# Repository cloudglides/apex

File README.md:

<h1 align="center">
  <br>

  <br>
  Apex
  <br>
</h1>
<h4 align="center">
A hub worth looking at.
</h4>
<div align="center">

</div>
<p align="center">
  <a href="#pcb">PCB</a> •
  <a href="#credits">Credits</a> •
  <a href="https://cad.onshape.com/documents/b957cb9eaff1fd55d943d2a3/w/8976d83a889d159a1f08a7bd/e/cf5443223244322f256cbf86">OnShape</a>
</p>

Apex is a custom usb hub PCB built around the Seeed FE1.1S, packing 1 upstream usb-c port, 2 downstream usb-a port.
Built because most usb hub don't let you own what's inside. Apex is made to be reproducible.

## PCB

Designed in KiCad with attention to power management, and equal traces. The board features a 2-layer optimized routing.

## How To build it?

Pretty simple actually, source all the components in BOM and assemble the pcb 
(the project uses smd components so get a pcba if you dont got prior experience)

## Why i made it?

- i wanted to make something
- i had nothing else to make
- i dont got a usb hub either and i really need it

### Schematic

---

### PCB Layers

#### Layer 1

#### Layer 2

---

### Board Views

#### Front

#### Back

### Zine

## Credits

This project uses:
- [KiCad](https://www.kicad.org/)
- [OnShape](https://cad.onshape.com/) for cad
- [Hack Club Fallout](https://fallout.hackclub.com)

## License

GPL

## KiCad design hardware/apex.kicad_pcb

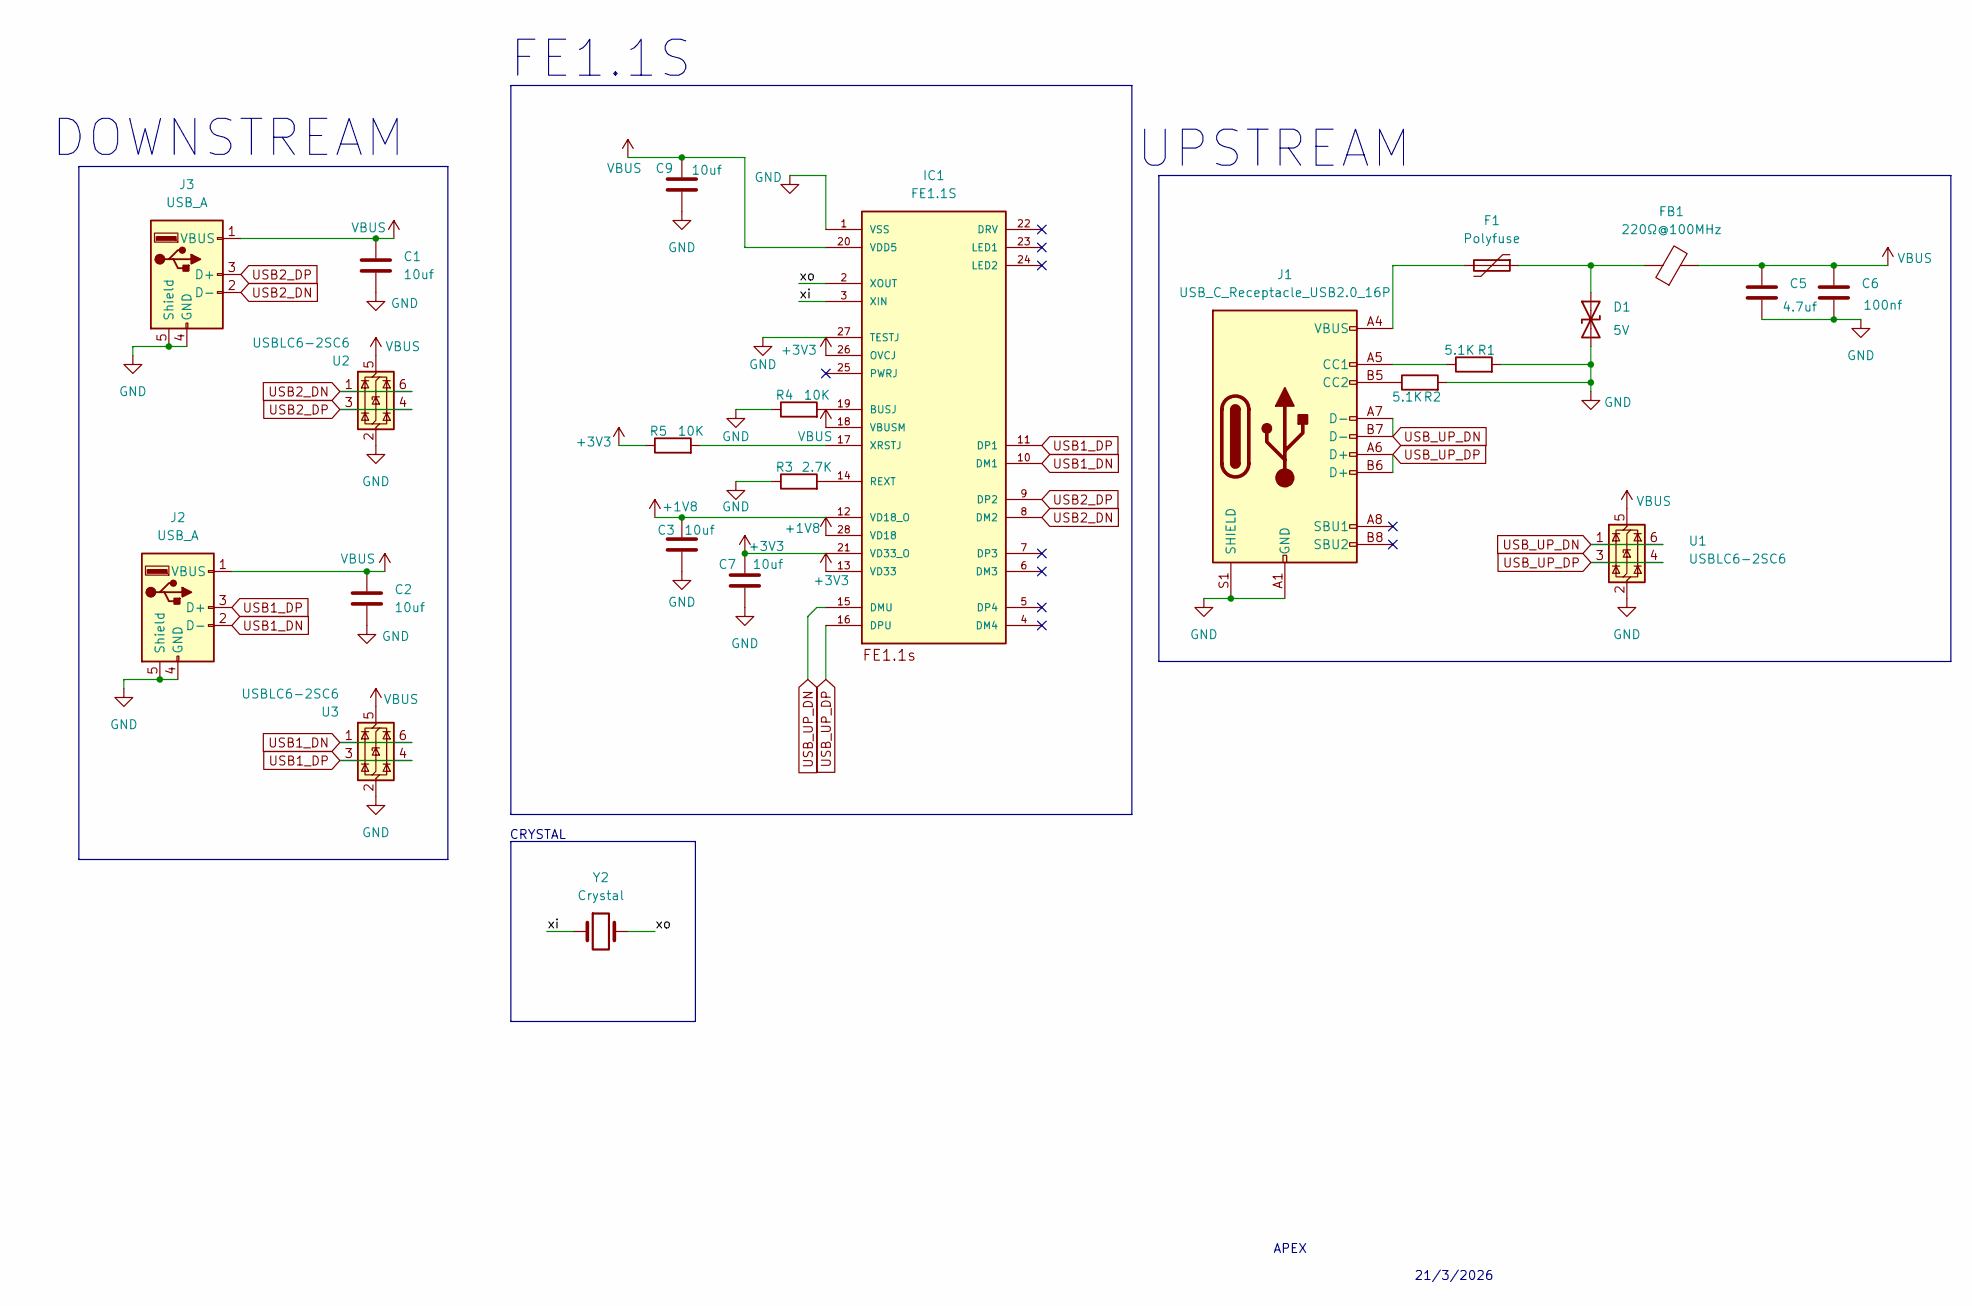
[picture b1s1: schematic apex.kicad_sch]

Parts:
C1, C2, C3, C7, C9: 10uf; C_0805_2012Metric
C5: 4.7uf; C_0805_2012Metric
C6: 100nf; C_0603_1608Metric
D1: 5V; D_SOD-123; LCSC Part C82044
F1: Polyfuse; Fuse_1206_3216Metric
FB1: 220Ω@100MHz; L_0603_1608Metric
IC1: FE1.1S; FE1.1S_SSOP-28
J1: USB_C_Receptacle_USB2.0_16P; USB_C_Receptacle_XKB_U262-16XN-4BVC11
J2, J3: USB_A; USB_A_Connfly_DS1095
R1, R2: 5.1K; R_0603_1608Metric
R3: 2.7K; R_0603_1608Metric
R4, R5: 10K; R_0603_1608Metric
U1, U2, U3: USBLC6-2SC6; SOT-23-6
Y2: Crystal; Crystal_SMD_HC49-SD

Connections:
+1V8: C3.1, IC1.12 (VD18_O), IC1.28 (VD18)
+3V3: C7.1, IC1.13 (VD33), IC1.21 (VD33_O), IC1.26 (OVCJ), R5.1
/xi: IC1.3 (XIN), Y2.1
/xo: IC1.2 (XOUT), Y2.2
GND: C1.2, C2.2, C3.2, C5.2, C6.2, C7.2, C9.2, D1.2 (A2), IC1.1 (VSS), IC1.27 (TESTJ), J1.A1 (GND), J1.A12 (GND), J1.B1 (GND), J1.B12 (GND), J1.S1 (SHIELD), J2.4 (GND), J2.5 (Shield), J3.4 (GND), J3.5 (Shield), R1.2, R2.2, R3.1, R4.1, U1.2 (GND), U2.2 (GND), U3.2 (GND)
unnamed: D1.1 (A1), F1.1, FB1.1
unnamed: F1.2, J1.A4 (VBUS), J1.A9 (VBUS), J1.B4 (VBUS), J1.B9 (VBUS)
unnamed: IC1.19 (BUSJ), R4.2
unnamed: IC1.14 (REXT), R3.2
unnamed: IC1.17 (XRSTJ), R5.2
unnamed: J1.A5 (CC1), R1.1
unnamed: J1.B5 (CC2), R2.1
USB1_DN: IC1.10 (DM1), J2.2 (D-), U3.1 (I/O1), U3.6 (I/O1)
USB1_DP: IC1.11 (DP1), J2.3 (D+), U3.3 (I/O2), U3.4 (I/O2)
USB2_DN: IC1.8 (DM2), J3.2 (D-), U2.1 (I/O1), U2.6 (I/O1)
USB2_DP: IC1.9 (DP2), J3.3 (D+), U2.3 (I/O2), U2.4 (I/O2)
USB_UP_DN: IC1.15 (DMU), J1.A7 (D-), J1.B7 (D-), U1.1 (I/O1), U1.6 (I/O1)
USB_UP_DP: IC1.16 (DPU), J1.A6 (D+), J1.B6 (D+), U1.3 (I/O2), U1.4 (I/O2)
VBUS: C1.1, C2.1, C5.1, C6.1, C9.1, FB1.2, IC1.18 (VBUSM), IC1.20 (VDD5), J2.1 (VBUS), J3.1 (VBUS), U1.5 (VBUS), U2.5 (VBUS), U3.5 (VBUS)

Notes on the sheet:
21/3/2026
CRYSTAL
FE1.1S
DOWNSTREAM
UPSTREAM
APEX

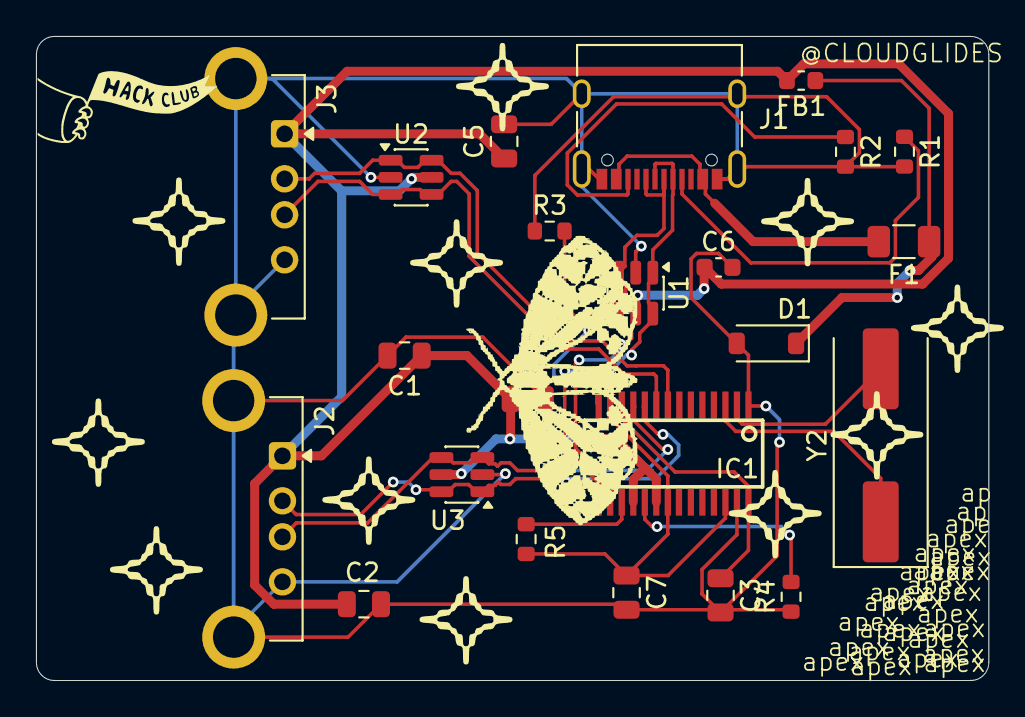
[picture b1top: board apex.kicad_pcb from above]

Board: 2 copper layers, 52.9 x 35.8 mm, 23 parts (0 on the bottom side), 19 nets.

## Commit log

2026-04-10 inital commit
2026-04-10 update: README with project overview and visuals
2026-04-13 add: BOM
2026-06-10 revise: apex_2
2026-06-10 Revise README with new images and improved text
    Updated images and text for clarity and consistency.
2026-06-16 Replace images in README with updated links
    Updated images in the README file to new sources.
2026-06-16 update: cad formats
2026-06-16 chore:update zine
2026-06-16 [ImgBot] Optimize images
    *Total -- 2,576.71kb -> 2,119.52kb (17.74%)
    /blender/Untitled.png -- 974.43kb -> 632.00kb (35.14%)
    /assets/public/banner.jpg -- 286.50kb -> 234.05kb (18.31%)
    /zine/zine.png -- 1,124.76kb -> 1,065.89kb (5.23%)
    /hardware/apex.png -- 191.02kb -> 187.57kb (1.81%)
2026-06-16 Add build instructions and motivation section to README
    Added a section on how to build the PCB and reasons for its creation.
